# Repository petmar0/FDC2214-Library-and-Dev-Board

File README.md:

# FDC2214-Library-and-Dev-Board
A library and sample dev board for the TI FDC2214 quad-channel capacitive touch sensor I2C ASIC.

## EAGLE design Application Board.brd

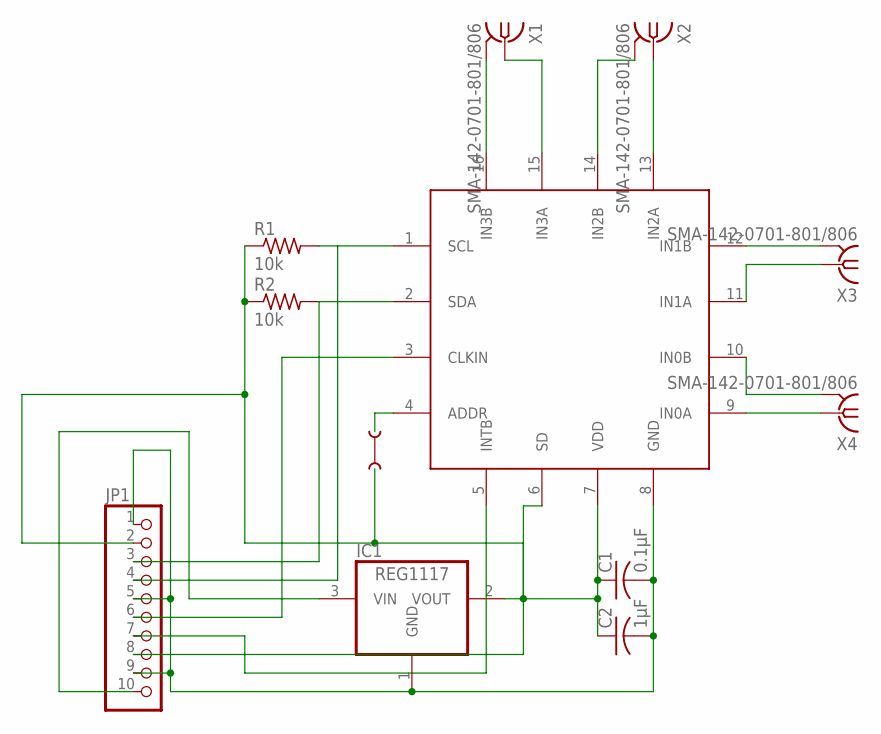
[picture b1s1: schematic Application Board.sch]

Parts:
C1: 0.1µF; C0402
C2: 1µF; C0402
IC1: REG1117; SOT223
J1: JUMP-Q; JUMP
JP1: PINHD-1X10; 1X10
R1, R2: 10k; M0805
U$1: FDC2214; QFN16-4X4
X1, X2, X3, X4: SMA-142-0701-801/806; J502-ND-142-0701-801/806

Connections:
unnamed: JP1.6, U$1.3 (CLKIN)
unnamed: C1.2, C2.2, IC1.1 (GND), JP1.1, JP1.5, JP1.9, U$1.8 (GND)
unnamed: C1.1, C2.1, IC1.2 (VOUT), JP1.2, R1.1, R2.1, U$1.7 (VDD)
unnamed: JP1.3, R2.2, U$1.2 (SDA)
unnamed: JP1.4, R1.2, U$1.1 (SCL)
unnamed: U$1.16 (IN3B), X1.G@1 (2), X1.G@2 (2), X1.G@3 (2), X1.G@4 (2)
unnamed: U$1.15 (IN3A), X1.1
unnamed: U$1.14 (IN2B), X2.G@1 (2), X2.G@2 (2), X2.G@3 (2), X2.G@4 (2)
unnamed: U$1.13 (IN2A), X2.1
unnamed: U$1.12 (IN1B), X3.G@1 (2), X3.G@2 (2), X3.G@3 (2), X3.G@4 (2)
unnamed: U$1.11 (IN1A), X3.1
unnamed: U$1.10 (IN0B), X4.G@1 (2), X4.G@2 (2), X4.G@3 (2), X4.G@4 (2)
unnamed: U$1.9 (IN0A), X4.1
unnamed: IC1.3 (VIN), JP1.10
unnamed: JP1.7, U$1.5 (INTB)
unnamed: JP1.8, U$1.6 (SD)

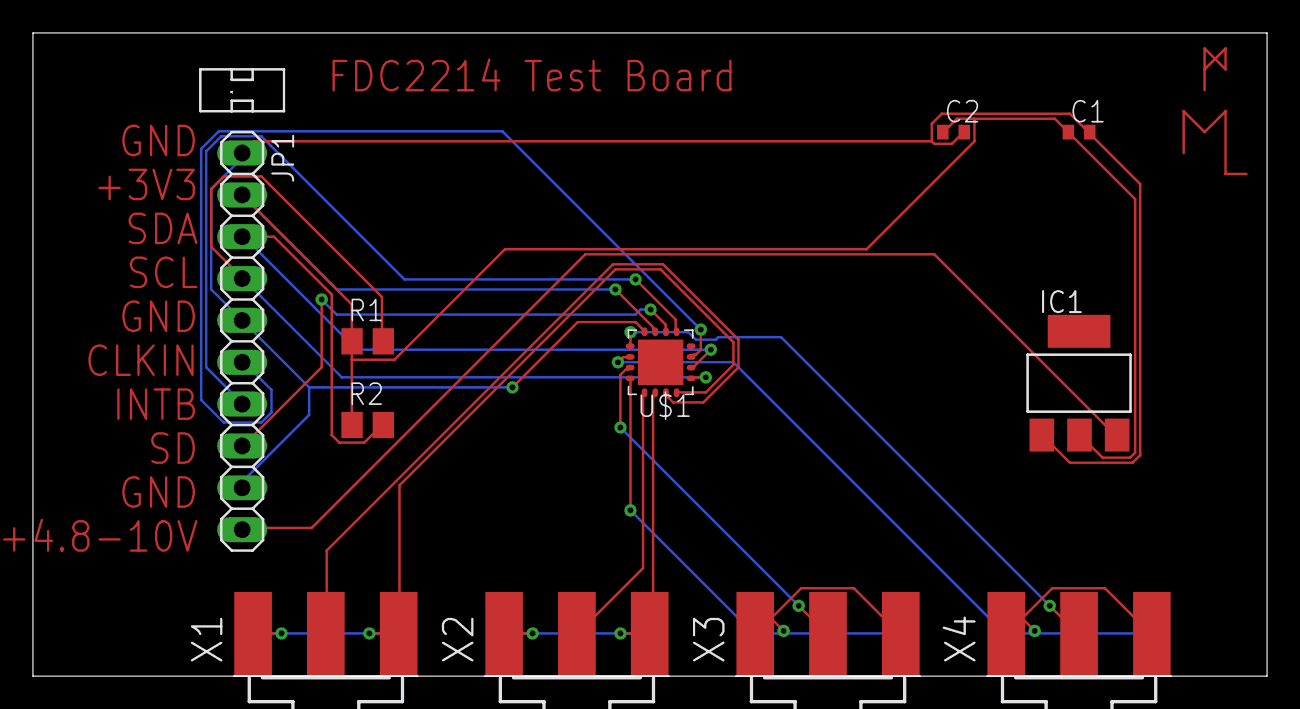
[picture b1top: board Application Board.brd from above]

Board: 2 copper layers, 74.9 x 39.0 mm, 12 parts (0 on the bottom side), 16 nets.

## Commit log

2017-07-03 Adding Datasheets
2017-07-03 Sense Boards
2017-07-03 Cleaning up files and adding PDFs
